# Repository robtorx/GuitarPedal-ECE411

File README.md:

# coolproject
ECE 411 - Fall 2023 - Team 12

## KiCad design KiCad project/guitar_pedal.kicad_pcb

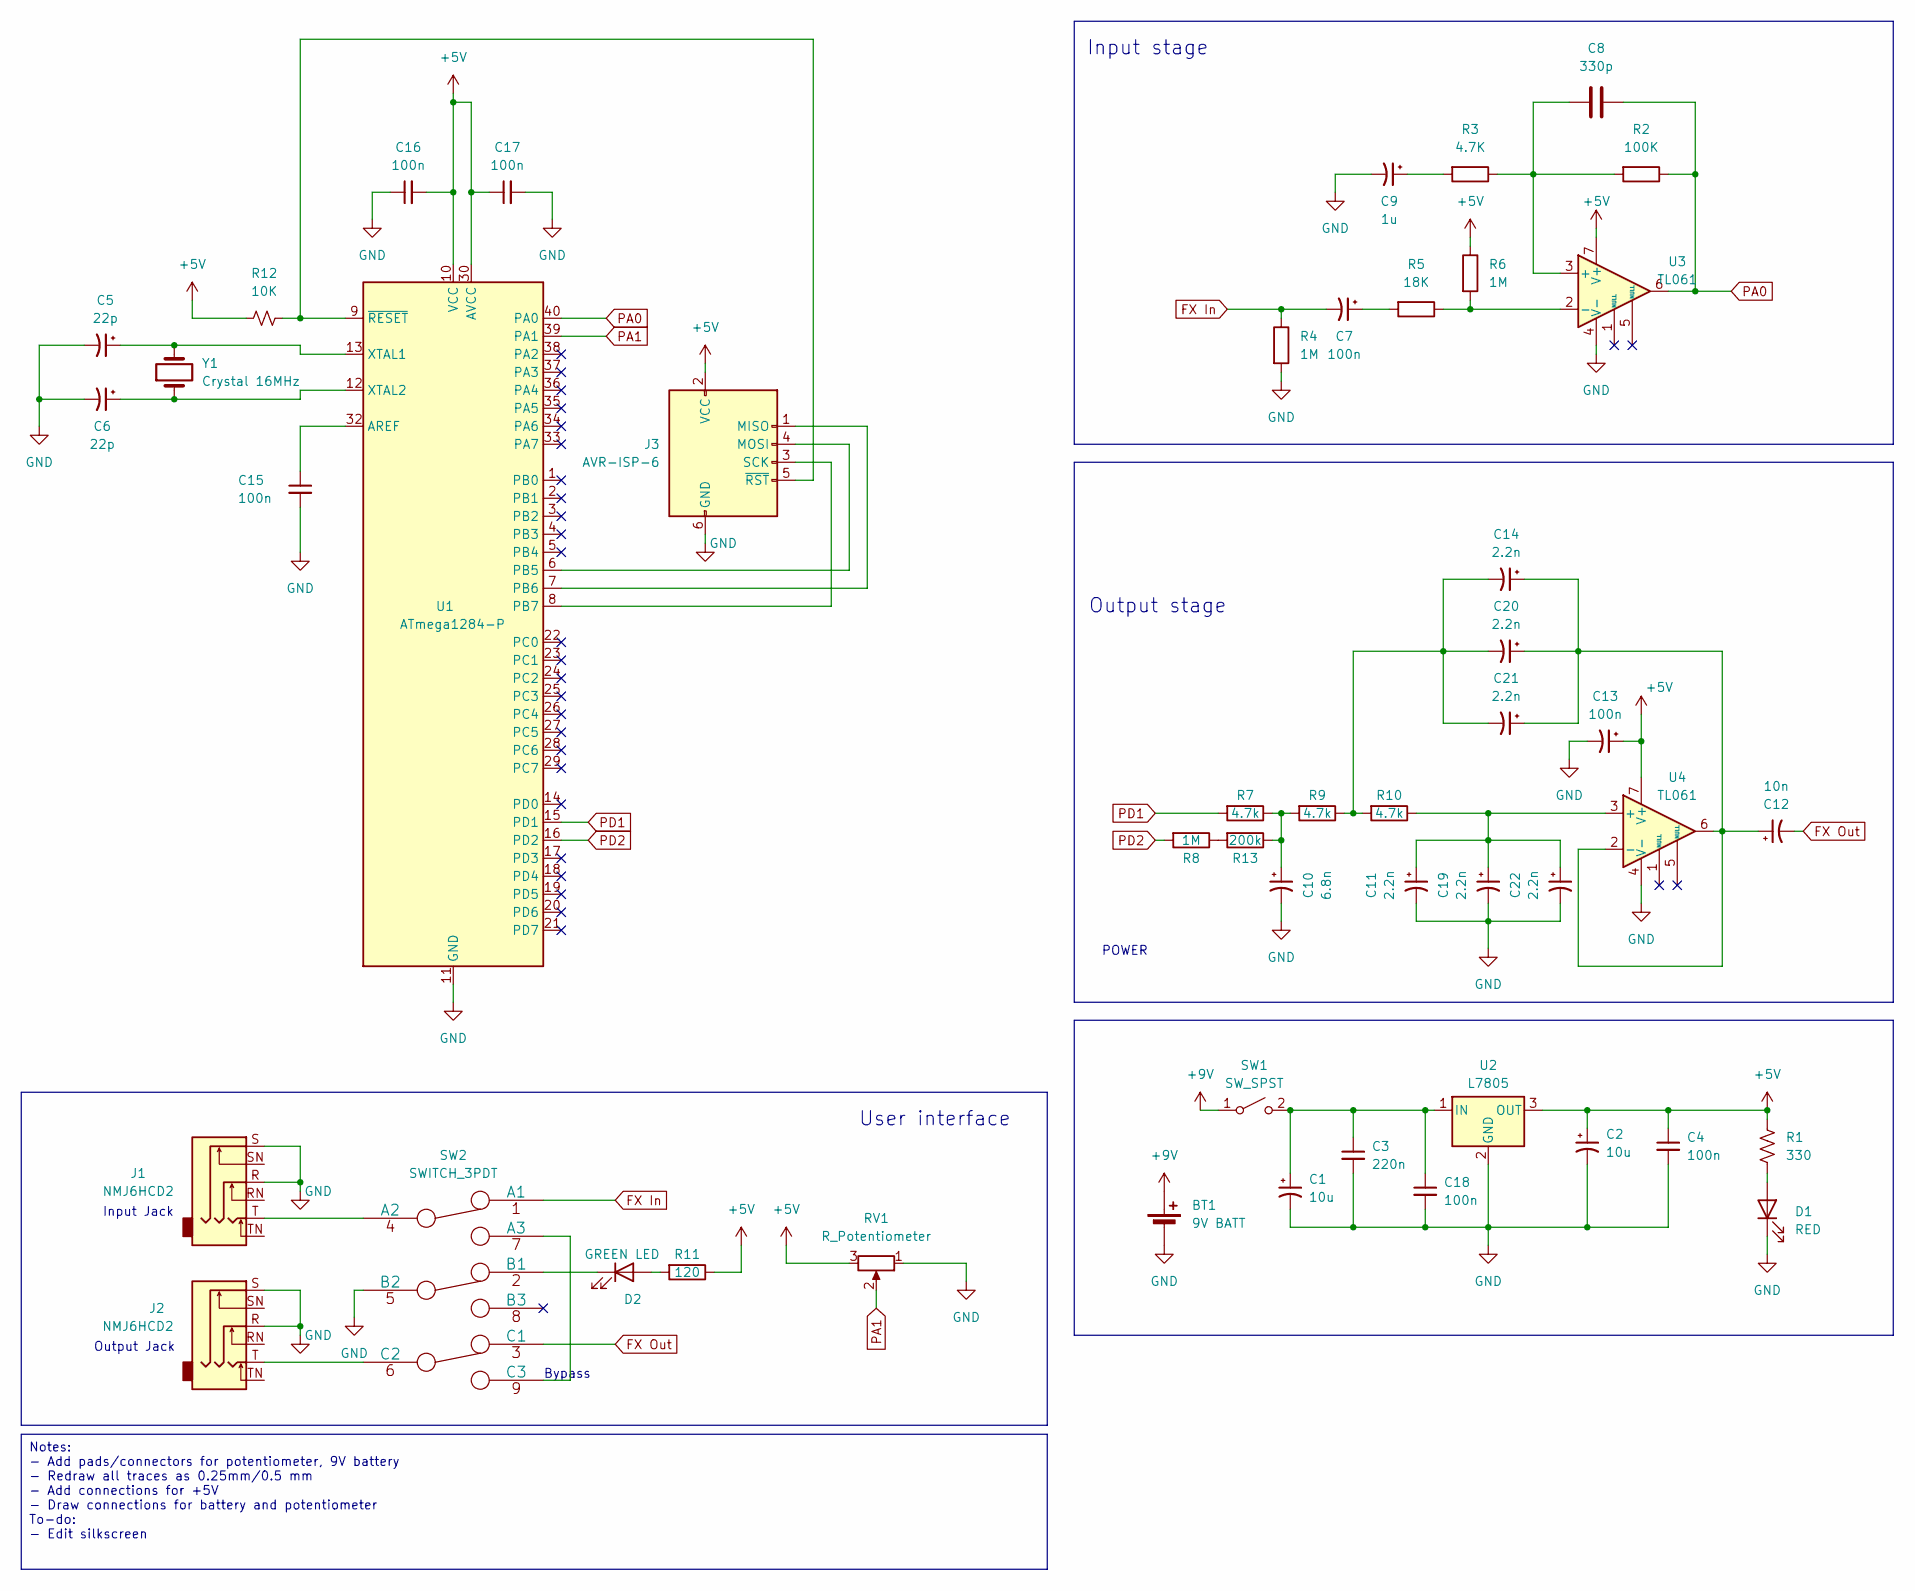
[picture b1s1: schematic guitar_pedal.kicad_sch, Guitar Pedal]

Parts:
BT1: 9V BATT; PinHeader_1x02_P2.54mm_Vertical
C1, C2: 10u; C_1206_3216Metric
C3: 220n; C_1206_3216Metric
C4, C7, C13, C15, C16, C17, C18: 100n; C_1206_3216Metric
C5, C6: 22p; C_1206_3216Metric
C8: 330p; C_1206_3216Metric
C9: 1u; C_1206_3216Metric
C10: 6.8n; C_1206_3216Metric
C11, C14, C19, C20, C21, C22: 2.2n; C_1206_3216Metric
C12: 10n; C_1206_3216Metric
D1: RED; LED_D3.0mm
D2: GREEN LED; LED_D3.0mm
J1, J2: NMJ6HCD2; Jack_6.35mm_Neutrik_NMJ6HCD2_Horizontal
J3: AVR-ISP-6
R1: 330; R_1206_3216Metric
R2: 100K; R_1206_3216Metric
R3: 4.7K; R_1206_3216Metric
R4, R6, R8: 1M; R_1206_3216Metric
R5: 18K; R_1206_3216Metric
R7, R9, R10: 4.7k; R_1206_3216Metric
R11: 120; R_1206_3216Metric
R12: 10K; R_1206_3216Metric
R13: 200k; R_1206_3216Metric
RV1: R_Potentiometer; PinHeader_1x03_P2.54mm_Vertical
SW1: SW_SPST; PinHeader_1x02_P2.54mm_Vertical
SW2: SWITCH_3PDT; 3PDT
U1: ATmega1284-P; TQFP-44_10x10mm_P0.8mm
U2: L7805; TO-220-3_Vertical
U3, U4: TL061; SOIC-8-1EP_3.9x4.9mm_P1.27mm_EP2.29x3mm
Y1: Crystal 16MHz; Crystal_HC49-U_Vertical

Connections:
+5V: C2.1, C4.1, C13.1, C16.2, C17.1, J3.2 (VCC), R1.1, R6.1, R11.1, R12.1, RV1.3, U1.10 (VCC), U1.30 (AVCC), U2.3 (OUT), U3.7 (V+), U4.7 (V+)
+9V: BT1.1 (+), SW1.1 (A)
FX In: C7.2, R4.1, SW2.1 (A1)
FX Out: C12.2, SW2.3 (C1)
GND: BT1.2 (-), C1.2, C2.2, C3.2, C4.2, C5.2, C6.2, C9.2, C10.2, C11.2, C13.2, C15.2, C16.1, C17.2, C18.2, C19.2, C22.2, D1.1 (K), J1.R, J1.S, J2.R, J2.S, J3.6 (GND), R4.2, RV1.1, SW2.5 (B2), U1.11 (GND), U1.31 (GND), U2.2 (GND), U3.4 (V-), U4.4 (V-)
unnamed: C7.1, R5.2
unnamed: C9.1, R3.2
unnamed: C10.1, R7.1, R9.2, R13.1
unnamed: C14.2, C20.2, C21.2, R9.1, R10.2
unnamed: D1.2 (A), R1.2
unnamed: D2.2 (A), R11.2
unnamed: D2.1 (K), SW2.2 (B1)
unnamed: J3.1 (MISO), U1.7 (PB6)
unnamed: J3.4 (MOSI), U1.6 (PB5)
unnamed: J3.3 (SCK), U1.8 (PB7)
unnamed: J3.5 (~RST), R12.2, U1.9 (~RESET)
unnamed: R8.1, R13.2
unnamed: C1.1, C3.1, C18.1, SW1.2 (B), U2.1 (IN)
unnamed: J1.T, SW2.4 (A2)
unnamed: SW2.7 (A3), SW2.9 (C3)
unnamed: J2.T, SW2.6 (C2)
unnamed: C15.1, U1.32 (AREF)
unnamed: C5.1, U1.13 (XTAL1), Y1.2
unnamed: C6.1, U1.12 (XTAL2), Y1.1
unnamed: C8.1, R2.2, R3.1, U3.3 (+)
unnamed: R5.1, R6.2, U3.2 (-)
unnamed: C11.1, C19.1, C22.1, R10.1, U4.3 (+)
unnamed: C12.1, C14.1, C20.1, C21.1, U4.2 (-), U4.6
PA0: C8.2, R2.1, U1.40 (PA0), U3.6
PA1: RV1.2, U1.39 (PA1)
PD1: R7.2, U1.15 (PD1)
PD2: R8.2, U1.16 (PD2)

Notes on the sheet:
Notes: - Add pads/connectors for potentiometer, 9V battery - Redraw all traces as 0.25mm/0.5 mm - Add connections for +5V - Draw connections for battery and potentiometer To-do: - Edit silkscreen
Output stage
Bypass
Input stage
User interface
POWER
Output Jack
Input Jack

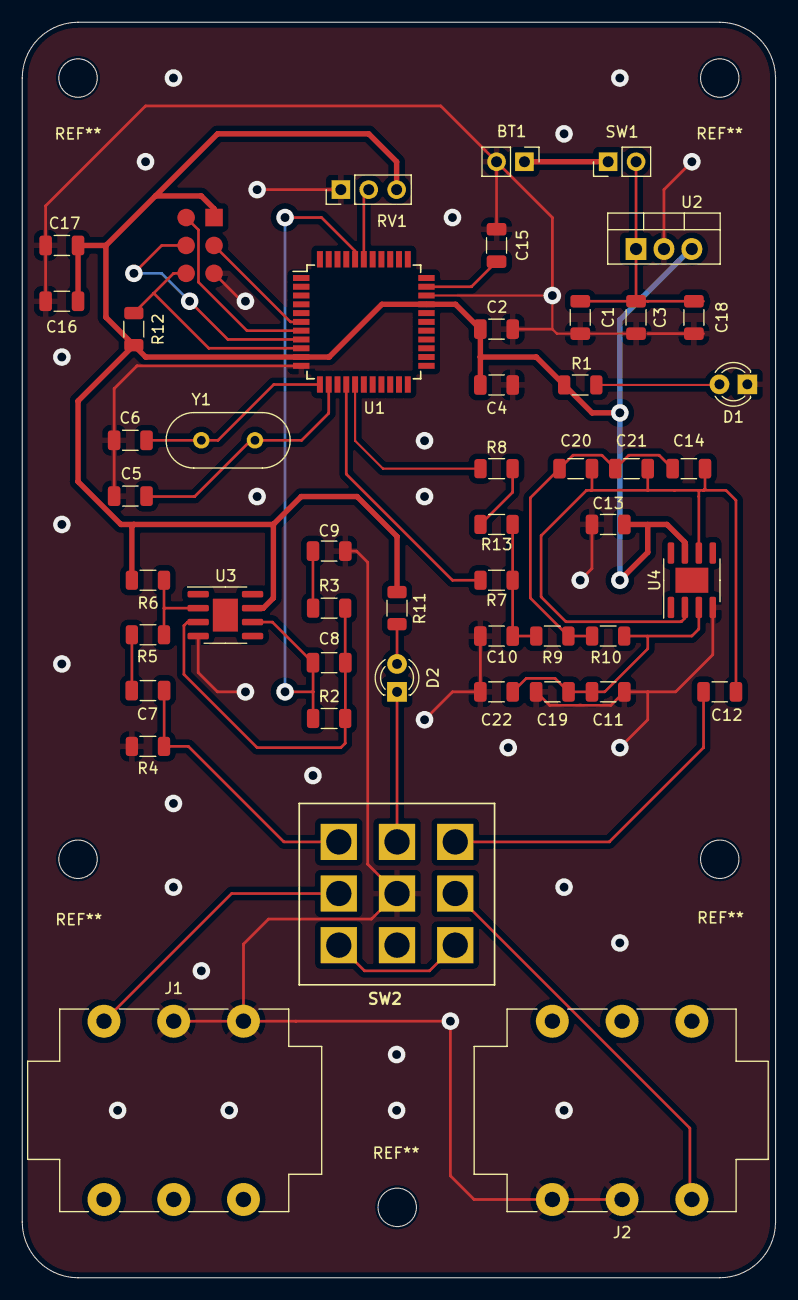
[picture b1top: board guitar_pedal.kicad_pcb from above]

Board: 2 copper layers, 68.6 x 114.3 mm, 49 parts (0 on the bottom side), 32 nets.

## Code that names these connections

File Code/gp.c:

/*
 * GuitarPedal.c
 *
 * Created: 11/13/23 12:47:54
 * Author : Rob
 */ 

#ifndef F_CPU
#define F_CPU 16000000UL	// 16MHz Clock Speed
#endif

#include <avr/io.h>
#include <util/delay.h>

#define PWM_FREQ 0x00FF   // pwm frequency - 31.3KHz
#define PWM_MODE 0    // Fast (1) or Phase Correct (0)
#define PWM_QTY 2   // 2 PWMs in parallel
int main(void)
{
  // SETUP
    //PD1 PD2 as output with PWM
      DDRD = 0x80;    //PD7 (pin21 - led) output. 
      //DDRD = 0x06  // Make just PD1 and PD2 output.
    // setup PWM
      TCCR1A = (((PWM_QTY - 1) << 5) | 0x80 | (PWM_MODE << 1)); //
      TCCR1B = ((PWM_MODE << 3) | 0x11);    // ck/1
      TIMSK1 = 0x20;    // interrupt on capture interrupt
      ICR1H = (PWM_FREQ >> 8);
      ICR1L = (PWM_FREQ & 0xff);
      DDRD |= 0x06;   // turn on PWM outputs PD1 and PD2
      sei();      // turn on interrupts  


    //PA0 PA1 as input both with ADC
      //PA0 Input (Pin40)
      ADMUX = 0x60;   // left adjust, adc0, internal vcc
      ADCSRA = 0xe5;  // turn on adc, ck/32, auto trigger
      ADCSRB = 0x07;  // t1 capture for trigger
      DIDR0 = 0x01;   // turn off digital inputs for adc0

                                                    
    }



    while (1) 
    {
		PORTD = 0x80;	//Turn on PD7
		_delay_ms(1000);
		PORTD = 0x00;	// Turn off PD7
		_delay_ms(1000);
    }
}

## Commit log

2023-10-24 Add files via upload
    initial schematic
2023-10-26 Added input/output op-amp buffer stages.
2023-10-31 Added bypass circuitry. Made edits to buffer stages + LED
2023-11-02 Reorganized files. Added initial PCB. Added KiCad components. Some footprints added to schematic.
2023-11-02 Added somes caps and resistors
2023-11-02 Work In Progress Breadboard
    Prototype has its 5V voltage regulator, a temporary 10K potentiometer, and a temporary ATmega1284PU. Will likely switch to QFP of Atmega. Currently using LM386N op amp until TL972 op amp arrives. Als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
2023-11-02 Changed some incorrect voltages.
    Still needs to consolidate 2 individual op amps into the TL972IDR, dual op amp.
2023-11-09 Overall schematic layout updated. Minor changes to components.
2023-11-09 Updated components with footprints, added to PCB
2023-11-10 Added traces to power supply and AVR modules in PCB.
2023-11-13 Updated schematic to match available components.
2023-11-13 Updates to PCB layout, most connections except ground/power added.
2023-11-13 Schematic Notes.PDF added.
2023-11-13 Minor changes to PCB
2023-11-14 Added remaining footprints to PCB, added ground plane and board edges.
2023-11-14 Added second layer. All connections on board. No errors in DRC, 200+ warnings.
2023-11-14 Updates to silkscreen
2023-11-15 Gerber files generated for 2 layer board.
2023-11-15 4 layer PCB version added (won't be used). Fixed Gerber files for 2 layer board to include mask/silk.
2023-11-16 Design review changes. Vias added, fixed capacitors in output stage.
2023-11-16 Fixed cap series to parallel. Includes updated PCB and Gerber files
2023-11-16 Minor fixes to silkscreen
2023-11-22 Led test code
2023-11-22 Create gp.c
    work in progress
2023-11-22 Create ledtest.c
    test led on PIN21
2023-11-30 11-30.c -- timer interrupt based code for POT0
2023-12-01 Added code plan documents.
2023-12-01 Create Test
2023-12-01 Update Test
2023-12-01 Rename Code/sketch_dec1a.ino to TEST
2023-12-02 EOF push (1201.c added). Code Plan to be updated.
2023-12-03 Added timer logic to 1201.c
2023-12-03 Updated Code Plan.docx. Added Timer ISR.
2023-12-05 Deleted code files. Added ADC toggle to 411pedal.c
2023-12-05 Added counter, code comments to 411pedal.c.
2023-12-05 Updated to PD6 and PD7 pinouts.
2023-12-05 Update 411pedal.c
    line 23 bool requires stdbool.h, not part of avr library, unsure if can be used.
    changed to:
    _Bool activeADC = false;
    line 133 assumed PRR0. power reduction register
    line 120 changed TICIE1 to ICIE1
    added function declerations line 28
2023-12-06 Housing STL files added
2023-12-06 Moved to TIMER1 interrupt
2023-12-07 Added Fusion files
2023-12-07 Robs version
2023-12-07 ADC trigger -> TIMER1. Delay.c added.
2023-12-07 Changes to delay.c to use PD4/5
2023-12-07 sinWave.c added.
